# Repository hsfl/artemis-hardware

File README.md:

<br>

# Artemis Cubesat Kit Hardware

This repository contains CAD models, Eagle designs, and thermal analysis for the Artemis Cubesat Kit V1.

For documentation and tutorials, visit our [project website](https://sites.google.com/hawaii.edu/artemiscubesatkit).

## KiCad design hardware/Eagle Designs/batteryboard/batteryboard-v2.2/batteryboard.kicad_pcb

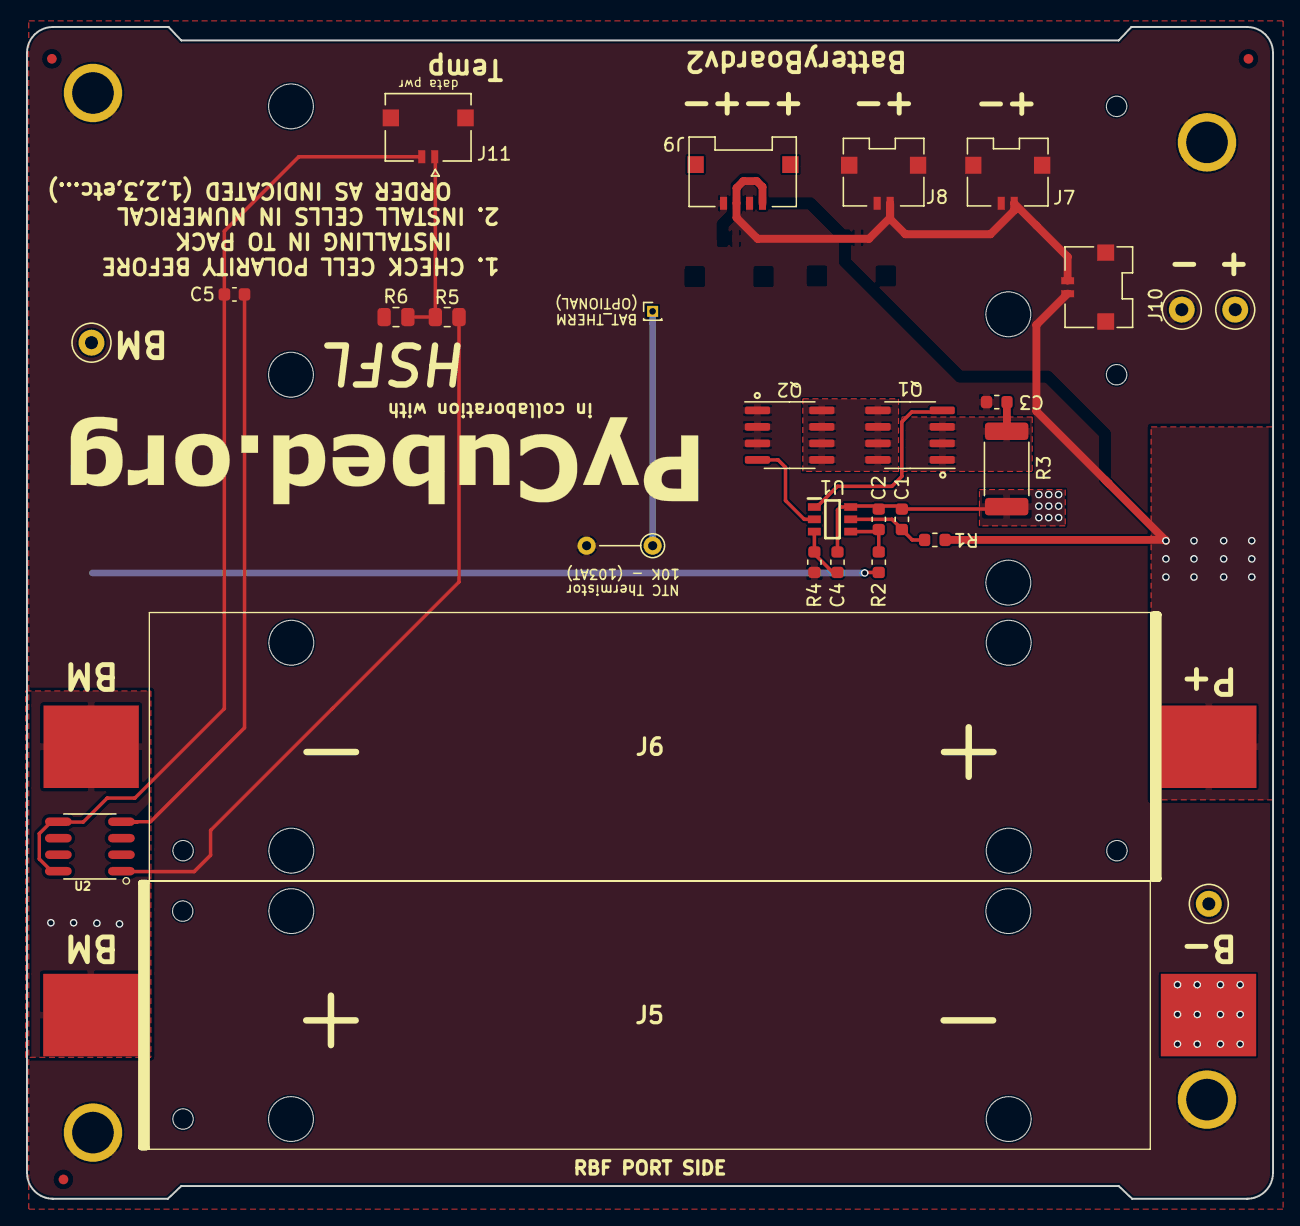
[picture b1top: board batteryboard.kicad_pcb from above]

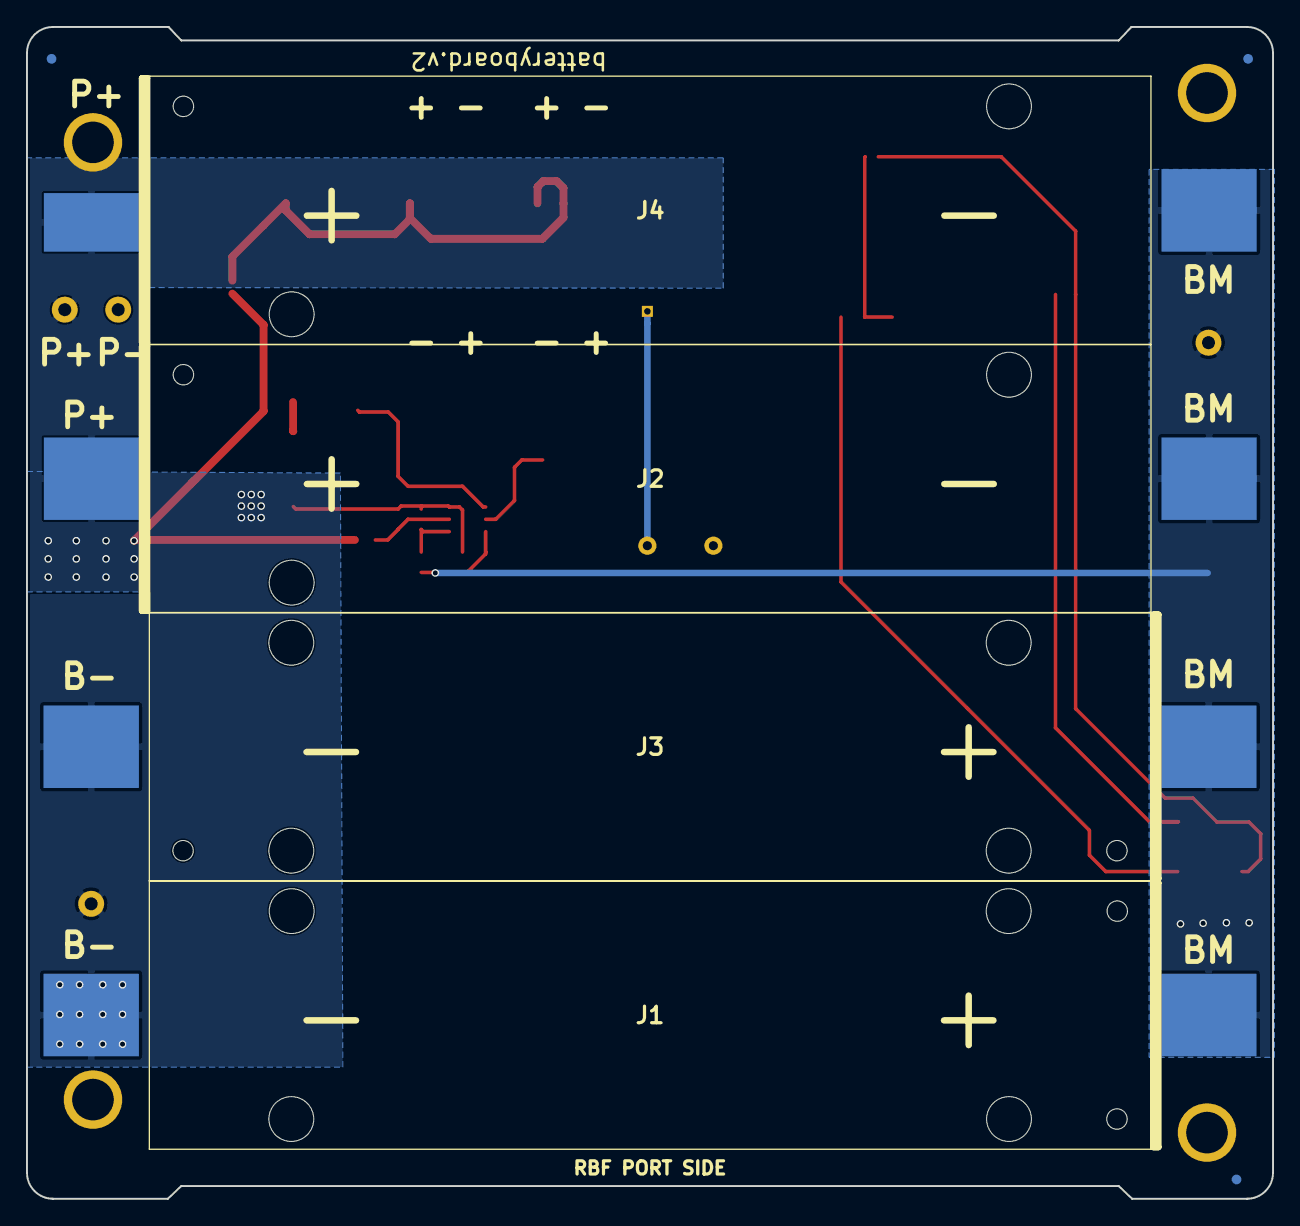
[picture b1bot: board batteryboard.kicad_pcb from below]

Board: 2 copper layers, 95.9 x 90.2 mm, 37 parts (4 on the bottom side), 16 nets.

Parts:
C1, C2, C3, C4, C5: 0.1uF; C_0603_1608Metric
H1, H2, H3, H4: MountingHole_Pad; MountingHole_3.2mm_M3_DIN965_PadMOD
J1, J2, J3, J4, J5, J6: KEYSTONE-1042
J7, J8, J10: Conn_01x02_Female; Molex_Pico-Lock_503763-0291_1x02-1MP_P1.00m_Horizontal
J9: Conn_01x04_Female; Molex_Pico-Lock_503763-0491_1x04-1MP_P1.00mm_Horizontal
J11: 5037630291; MOLEX_5037630291
J12: Screw_Terminal_01x01; PinHeader_1x01_P1.00mm_Vertical
Q1, Q2: IRF7458; SOIC-8_3.9x4.9mm_P1.27mm
R1, R2: 330; R_0603_1608Metric
R3: 0.01; R_2512_6332Metric
R4: 1K; R_0603_1608Metric
R5: 45.3k; R_0805_2012Metric
R6: 10k; R_0805_2012Metric
Ref**: Val**; pycubed_logo
TH1: Thermistor; R_Axial_DIN0204_L3.6mm_D1.6mm_P5.08mm_Vertical
TP1, TP2, TP3, TP4: TestPoint; TestPoint_Loop_D1.80mm_Drill1.0mm_Beaded
U1: R5460N233AF; SOT95P280X130-6N
U2: TMP36FSZ; SOIC8P127_490X600X175L83X41N

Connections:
/VDD: C1.2, R1.2, U1.5
B-: C1.1, C2.1, C4.1, J1.1, J3.1, J5.1, R3.1, TP1.1, U1.6
BAT_THERM: J12.1, TH1.1
BM: J1.2, J2.1, J3.2, J4.1, J5.2, J6.1, R2.1, TP2.1
unnamed: C2.2, R2.2, U1.4
unnamed: C3.1, Q1.1, Q1.2, Q1.3, R3.2
unnamed: C4.2, R4.1, U1.3
unnamed: C5.1, J11.2, U2.5, U2.8
unnamed: J7.1, J8.1, J9.1, J9.3, J10.2
unnamed: J11.1, R5.2, R6.1
unnamed: Q1.4, U1.1
unnamed: Q1.5, Q1.6, Q1.7, Q1.8, Q2.5, Q2.6, Q2.7, Q2.8
unnamed: Q2.4, U1.2
unnamed: R5.1, U2.1
PACK+: J2.2, J4.2, J6.2, J10.1, R1.1, TP4.1
PACK-: C3.2, C5.2, H1.1, H2.1, H3.1, H4.1, J7.2, J8.2, J9.2, J9.4, J11.S1, J11.S2, Q2.1, Q2.2, Q2.3, R4.2, R6.2, TH1.2, TP3.1, U2.4

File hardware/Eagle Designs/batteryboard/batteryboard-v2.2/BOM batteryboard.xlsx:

Id | Designator | Package | Quantity | Designation | Supplier and ref | Column1 | _1
1 | R6 | R_0805_2012Metric | 1 | 10k
2 | R5 | R_0805_2012Metric | 1 | 45.3k
3 | J2,J4,J6,J5,J3,J1 | KEYSTONE-1042 | 6 | KEYSTONE-1042
4 | Ref** | battery_version | 1 | Val**
5 | H3,H4,H2,H1 | MountingHole_3.2mm_M3_DIN965_PadMOD | 4 | MountingHole_Pad
6 | Ref** | pycubed_logo | 1 | Val**
7 | REF**,REF**,REF**,REF**,REF**,REF** | Fiducial_0.75mm_Mask1.5mm | 6 | Fiducial_0.75mm_Mask1.5mm
8 | TH1 | R_Axial_DIN0204_L3.6mm_D1.6mm_P5.08mm_Vertical | 1 | Thermistor
9 | J12 | PinHeader_1x01_P1.00mm_Vertical | 1 | Screw_Terminal_01x01
10 | TP4,TP3,TP2,TP1 | TestPoint_Loop_D1.80mm_Drill1.0mm_Beaded | 4 | TestPoint
11 | C3,C4,C2,C1,C5 | C_0603_1608Metric | 4 | 0.1uF
12 | R4 | R_0603_1608Metric | 1 | 1K
13 | R2,R1 | R_0603_1608Metric | 2 | 330
14 | R3 | R_2512_6332Metric | 1 | 0.01
15 | Q2,Q1 | SOIC-8_3.9x4.9mm_P1.27mm | 2 | IRF7458
16 | U1 | SOT95P280X130-6N | 1 | R5460N233AF
17 | J7,J8,J10,J11 | Molex_Pico-Lock_503763-0291_1x02-1MP_P1.00m_Horizontal | 4 | Conn_01x02_Female
18 | J9 | Molex_Pico-Lock_503763-0491_1x04-1MP_P1.00mm_Horizontal | 1 | Conn_01x04_Female
19 | U2 | TMP36FSZ-REEL | 1 | TMP36FSZ-REEL

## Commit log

2020-08-04 Transfer repo
2020-08-04 Scripts
2020-09-28 Removed doxygen output
2020-11-10 Create CAD model
2020-11-10 Rename README to README.md
2020-11-10 Rename README.md to README.txt
2020-11-12 Updated deploy
2020-12-08 Moved hardware files
2021-02-19 organizing the hardware folder, adding an Eagle folder for our designs
2021-02-19 Adding BOM
2021-02-19 Surface mount connectors connected to ground
2021-02-19 Moved solar panel boards to Eagle folder, deleted redudant OBC files
2021-02-26 OBC Board changes
    Switched out thru-hole connectors with Molex connectors; added ethernet and USB OTG connectors from BBB to OBC board and ethernet/USB OTG external connectors
2021-02-26 Removed unnecessary OBC backup files
2021-03-01 Added payload board Eagle files
2021-03-06 Edited payload board, created payload and bbb obc BOM
2021-03-09 Update payload board
2021-03-09 Update Payload board file
2021-03-09 Payload board changes
2021-03-09 Updated solar panel boards
2021-03-10 Solar panel board changes
    Added temp sensor and external connector to solar panel board; updated solar panel board BOM
2021-03-19 Added antenna board Eagle files and BOM
2021-04-20 Uploaded Eagle project files
2021-05-06 Uploaded Solar Panel Board v2
2021-05-06 Added values to resistors and capacitors
    Payload - added 3.3k value to pullup resistors for H-bridges
    Solar Panel Board - added 0.1uF value to capacitor for temp sensor
2021-05-06 Updated BOMs and edited Solar Panel Board v2
2021-05-07 Add files via upload
    Edited Solar Panel Board v2
2021-05-29 Uploaded H-bridge library and design block files
2021-05-29 added PDU v2 Eagle files and Artemis Library
2021-06-01 updated PDU v2 Eagle files and Artemis Library
2021-06-04 updated PDU v2 H Bridge Circuit Design
2021-06-04 Uploaded Eagle libraries
2021-06-07 Updated Solar Panel BOM
2021-06-11 updated PDU v2 and Artemis Library
2021-06-22 updated PDU v2 Microprocessor schematic
2021-06-29 updated PDU v2
2021-06-30 Updated antenna and solar panel boards.
2021-07-01 updated PDU v2 schematic
2021-07-01 Updated antenna and solar panel boards
2021-07-09 updated PDU v2 (pre-routing)
2021-07-14 Uploaded OBC version 2
2021-07-27 Changed connectors for RBF pin and moved in connectors that interfered with structure.
2021-07-30 updated PDU v2 (Routing Rough Draft complete)
2021-08-10 OBC version 3 is finally here
2021-08-11 Revised OBC v3 and BB v2
2021-08-13 made minor changes to the OBC and BB
2021-09-02 fixed naming issues
2021-09-03 uploaded completed PDU v2
2021-09-09 made improvements to the solar panel board and included cam outputs
2021-09-11 completed PDU v2
2021-10-01 Artemis V1.2 R2
2021-10-06 uploaded Camera Mount Board schem and board; removed PDU v2 screw terminal
2021-10-12 replaced PDU v2 terminal with Conn Header 0.1'
2021-10-12 Created OBC_v4
2021-10-12 Uploaded OBC_v4 BOM
2021-10-12 Solar panel board v6
2021-10-13 Updated OBC and Solar Panel boards
2021-10-14 added HSFL stencil logo to Camera Mount Panel Board
2021-10-16 OBC v4 edits
2021-11-09 Added Eagle files for EPET payload
2021-11-09 Added antenna board v3, removed extra antenna board v2 files
2021-11-10 Uploaded solar panel board v6.1
2021-11-10 Battery board text changes
2021-11-13 Updated scintillator detector PCB
2021-11-15 Updated solar panel board temp sensor circuit
2021-11-15 Edited temp sensor circuit on battery board
2021-11-15 Updated temp sensor circuit for scintillator pcb
2021-11-15 Changed scintillator temp sensor
2021-11-17 Scintillator detector edits
2021-11-18 Added text to bottom and top of board to denote connectors + temp sensor/torque coils
2021-11-24 updated PDU v2, added Battery Charging Circuit design block
2021-11-30 added PDU v2 Revisions
2021-12-01 Edited detector pcb and created battery charging circuit board
2021-12-07 updated OBC v4 with Teensy Rough Draft
2021-12-08 updated OBC v4.1; verified & updated Battery Charging Circuit
2021-12-08 Finalized PDU Battery Charging Circuit Design And Added Gerber Files
2021-12-10 Edited antenna board and battery board
2021-12-15 Latest CAD update
2021-12-22 Completed OBC v4.1 (Finished); Updated PDU v2.1 (Unfinished)
2021-12-22 Updated OBC v4.1
2021-12-24 updated OBC v4.1. with revision feedback
2021-12-30 Updated antenna board
2022-01-05 Added microUSB connector to antenna board
2022-01-06 uploaded Chris Noon's server and client
2022-01-07 Made edits to solar panel, antenna, battery boards
2022-01-19 completed PDU v2.1 revisions 01/18/2022 and did minor changes to OBC v4.1
2022-01-20 did OBC v4.1 revisions (replaced Antenna connector); uploaded OBC Eagle Library
2022-02-03 did OBC and PDU revisions (02/03/2022)
2022-02-08 updated PDU v2.1 (02/08/2022) before major changes
2022-02-15 updated OBC v4.20 (02/15/2022)
2022-02-18 finalized OBC v4.20; updated PDU v2.1
2022-02-18 revised and finalized OBC v4.20, added OBC v4.20 BOM and Gerber Files
2022-02-23 Antenna board edits
2022-02-25 updated PDU v2.1 (ongoing board cleanup)
2022-03-01 completed PDU v2.1 (awaiting feedback)
2022-03-08 finalized PDU v2.1 and generated Gerber Files
2022-03-15 added Kapton Heater Connector (device) to PDU v2.1
2022-03-17 Switched the Teensy UART pins on OBCv4.21
2022-03-30 Antenna board silkscreen edits
2022-04-08 Updated OBC v4.21 with 2 Radios, Added SPI to PC 104 Header, Uploaded Radio Devices Eagle Library
2022-04-08 Corrected SPI Connections to PC 104 Header
2022-04-14 fixed OBC modular radio Radio Reset connection
2022-04-21 uploaded official OBC v4.21
2022-05-11 Created PDU v2.2; First edit
2022-07-27 created OBC v4.22 and uploaded revised Teensy Library
2022-07-27 updated PDU v2.2
2022-07-29 Antenna Board hole changes
2022-08-31 Eagle battery board
2022-09-10 completed OBC v4.23
2022-09-10 updated and finalized OBC V4.23
2022-09-23 Added v2 boards
2022-09-23 Removed unnecessary v2 backup Eagle files; added newest OBC revision
2022-10-12 OBC Organization
2022-11-02 OBC 4.24
2022-11-02 OBC_V4.24
2022-11-03 added power labels to R8, R9 of OBC V4.24
2022-12-01 OBC V4.24
2022-12-02 cleaned up a wire stub on OBC 4.24 and copied OBC for RF with ground plane
2022-12-02 renamed OBC 4.24_RFplane
2022-12-03 Added RF plane to OBCv4.24
2022-12-03 changed radio power supply from 5V_bus to SW_3V3_2 on both the OBCv2.24 and OBCv2.24_RFplane. Added ground station board.
2022-12-06 Renamed and reorganized Artemis v2 boards
2022-12-06 Created an Artemis v2 battery board
2022-12-08 add PDUv2.0 board and schematic
2022-12-08 Updated Artemis v2 EAGLE libraries and removed
2022-12-09 Updated Artemis v2 EAGLE library, solar panel board, and antenna board
2023-02-03 added VIA to GND Plane for PDU V2.2
2023-02-16 Swapped the antenna pad for the MCX connector on the ground station board. Created the mock transmission board which is a radio, teensy and antenna.
2023-02-17 Added RF ground plane to ground station board.
2023-02-28 Modified pin configuration on the ground station board to match OBC 4.24.
2023-03-01 fixed OBC, PDU for Manufacturing Order
2023-03-14 fixed PDU for manufacturing
2023-03-23 Fixed RF ground station board... again.
2023-05-11 cleaned up
2023-05-11 fix broken image paths and update website url
2023-05-12 fix broken image paths, update website url, and clean up
2023-05-18 Battery Board V2 changes
2023-05-18 Battery Board V3 Changes
2023-05-19 Solar Panel and Antenna Board Edits
2023-06-21 Board updates
2023-08-31 ArtemisR4
    Updated Artemis Structure for lab.
2023-08-31 Updated Structure Model for Lab
2023-11-21 Add files via upload
    Thermal Desktop files
2024-01-19 reorganize
2024-02-29 add simulator
2024-02-29 add detumbling-simulator as a git module
